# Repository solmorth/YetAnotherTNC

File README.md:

# YetAnotherTNC

Zephyr firmware (and, eventually, a companion PCB) for a nRF52840 Pro Micro
board that turns a phone's Bluetooth connection into a packet radio TNC.
Depending on how three GPIO pins are strapped at boot, the board acts as a
transparent UART↔BLE bridge, a real AX.25/KISS TNC driving 1200 baud Bell 202
AFSK audio (with optional FX.25 FEC), an AX.25 digipeater, or a standalone GPS
APRS tracker that beacons its position with no phone attached.

> **Early stage.** This has not been widely field-tested — one unit rides in
> the author's car and works there, but it hasn't been validated across
> different radios, conditions, or by other users. Treat it as a hobby
> project that works, not a hardened product.

No app or phone-side code lives in this repo — this is the board (and PCB)
side only. Anything that speaks BLE Nordic UART Service (NUS) and either raw
KISS or TNC2 monitor lines can talk to it; see [Phone app](#phone-app) below.

## Contents

- [Why](#why)
- [Hardware](#hardware)
  - [PCB](#pcb)
  - [Pinout](#pinout)
  - [Transceiver connector (JST 10-pin)](#transceiver-connector-jst-10-pin)
  - [Bill of Materials (BOM)](#bill-of-materials-bom)
- [Operating modes](#operating-modes)
- [Runtime configuration](#runtime-configuration)
- [Known limitations](#known-limitations)
- [Phone app](#phone-app)
- [Building](#building)
  - [Releases](#releases)
- [Testing](#testing)
- [Hardware-in-the-loop (HIL) test plan](#hardware-in-the-loop-hil-test-plan)
- [Repo layout](#repo-layout)
- [License](#license)

## Why

Cheap handheld radios generally don't have a KISS/TNC mode, and dedicated TNC
hardware is either bulky or costs more than the radio. This is a ~$10 nRF52840
board wired to a radio's mic/speaker/PTT lines, doing the AFSK modem and
AX.25 framing in software, with a phone or laptop over BLE instead of a serial
cable.

## Hardware

**Primary target: Yaesu FTM510.** The board's connector is designed to match
the FTM510's mic/data jack. The **FTM400 works out of the box** — same
connector, same signals. Any other radio that can be driven by its
mic/speaker/PTT lines can work too, via a custom audio interface cable
(not covered by this repo — just the pins on the nRF52840 side).

Board: Pro Micro nRF52840 (or any nice!nano-bootloader-compatible clone,
`promicro_nrf52840` in Zephyr).

### PCB

PCB design files and bill of materials live under [`pcb/`](pcb/) (`yatnc.kicad_sch`, `yatnc.kicad_pcb`, `yatnc.csv`).

| PCB 3D Render | PCB Editor |
|:---:|:---:|
|  |  |

### Pinout

| Pin | DT node | Function | Notes |
|---|---|---|---|
| 9, 10 (P0.09/P0.10) | `uart0` | Radio RS232 (APRS data) | Level-shifted through an onboard MAX3232 to true RS-232 (±12V). Primary use: the FTM510/FTM400's own built-in APRS packet decoder outputs RS232 here in BRIDGE mode. Also works with other serial-speaking radios/modems that expect a native protocol. Never touched by firmware for anything else. |
| 31 (P0.31) | `zephyr,user` io-channel | RX audio in | ADC (AIN7), sampled at 9600 Hz for the AFSK demodulator. |
| 20 (P0.20) | `&pwm0_default` | TX audio out | Hardware PWM carrier, low-pass filtered externally into an analog tone. |
| 22 (P0.22) | `ptt_pin` | PTT out | Active-high. |
| 2 (P0.02) | `mode_pin` | Mode select | Pull-up, active-low. Grounded → PACKET_TNC. |
| 29 (P0.29) | `digi_pin` | Digipeater select | Pull-up, active-low. Grounded → DIGIPEATER (overrides pin 2). |
| P1.15 | `standalone_pin` | Standalone GPS select | Pull-up, active-low. Grounded → STANDALONE (overrides pins 2 and 29). |
| P0.11 / P1.00 | `uart1` | GPS NMEA in | 9600 baud, TX / RX respectively (the GPS module's RX / TX). Only used in STANDALONE mode. |
| P1.04 | `gps_enable_pin` | GPS power enable | Active-high, pulled down. Driven high at boot in STANDALONE mode (unless a fixed position is configured). |

### Transceiver connector (JST 10-pin)

> [!IMPORTANT]
> - **RS-232 voltage levels (±12V)**: The serial lines on the 10-pin JST connector (`TO TRCV`) are true **RS-232 (±12V)** driven by the onboard MAX3232 transceiver, **not** 3.3V or 5V TTL. Do not connect them directly to logic-level UART pins!
> - **RX / TX crossover**: The RS-232 RX and TX lines **must be crossed** between the board's 10-pin JST connector and the radio (Board TX &rarr; Radio RX, Board RX &rarr; Radio TX).

| Pin | Net | Function / Description |
|:---:|---|---|
| 1 | `PKD` | TX Packet Audio (from PWM filter) |
| 2 | `GND` | Ground |
| 3 | `PTT` | PTT output |
| 4 | NC | Unconnected |
| 5 | `AUDIO TRCV` | RX Audio (to ADC demodulator) |
| 6 | NC | Unconnected |
| 7 | `RX` | RS-232 RX (±12V, connect to Radio TX — **crossed**) |
| 8 | `TX` | RS-232 TX (±12V, connect to Radio RX — **crossed**) |
| 9 | NC | Unconnected |
| 10 | NC | Unconnected |

### Bill of Materials (BOM)

Generated from KiCad BOM ([`pcb/yatnc.csv`](pcb/yatnc.csv)):

| Designator | Value / Part | Qty | Description |
|---|---|:---:|---|
| C1 | 270µF 35V | 1 | Polarized electrolytic capacitor |
| C2, C4, C7, C8, C9, C10, C11, C12 | 100nF | 8 | Ceramic disc capacitor |
| C3, C5 | 5.6nF | 2 | Ceramic disc capacitor |
| C6 | 470µF 10V | 1 | Polarized electrolytic capacitor |
| D1 | LPWR | 1 | Power indicator LED (5mm) |
| D2 | 1N5822 | 1 | Schottky diode (3A, 40V) |
| D3 | BZW04 18V | 1 | TVS transient voltage suppressor diode |
| D4 | LPTT | 1 | PTT indicator LED (5mm) |
| D5 | 1N4148 | 1 | High-speed switching diode |
| IC1 | MAX3232CDR | 1 | 3.3V/5V RS-232 transceiver (SOIC-16) |
| J1 | Conn_02x03_Top_Bottom | 1 | 2×3 pin header (2.54mm pitch) |
| J4 | DFR0570 | 1 | DFRobot DFR0570 DC-DC buck converter module |
| J5, J6 | Conn_01x13_Socket | 2 | 1×13 female socket headers (for Pro Micro nRF52840) |
| J7 | Conn_01x04_Pin | 1 | JST-EH 4-pin vertical header (2.50mm pitch) |
| PWR | Conn_01x02_Socket | 1 | JST-EH 2-pin vertical power connector (2.50mm pitch) |
| Q1, Q2 | BC547 | 2 | NPN bipolar junction transistor (TO-92) |
| R1, R3, R4, R5, R10 | 1k | 5 | Axial resistor 1kΩ (DIN0207) |
| R2 | 1ohm | 1 | Axial resistor 1Ω (DIN0207) |
| R6, R7, R8, R9 | 10k | 4 | Axial resistor 10kΩ (DIN0207) |
| SW1 | RST | 1 | Tactile push button switch (6mm) |
| TO TRCV | JST | 1 | JST-EH 10-pin vertical connector (to transceiver) |

### Transceiver connector (JST 10-pin)

> [!IMPORTANT]
> - **RS-232 voltage levels (±12V)**: The serial lines on the 10-pin JST connector (`TO TRCV`) are true **RS-232 (±12V)** driven by the onboard MAX3232 transceiver, **not** 3.3V or 5V TTL. Do not connect them directly to logic-level UART pins!
> - **RX / TX crossover**: The RS-232 RX and TX lines **must be crossed** between the board's 10-pin JST connector and the radio (Board TX &rarr; Radio RX, Board RX &rarr; Radio TX).

| Pin | Net | Function / Description |
|:---:|---|---|
| 1 | `PKD` | TX Packet Audio (from PWM filter) |
| 2 | `GND` | Ground |
| 3 | `PTT` | PTT output |
| 4 | NC | Unconnected |
| 5 | `AUDIO TRCV` | RX Audio (to ADC demodulator) |
| 6 | NC | Unconnected |
| 7 | `RX` | RS-232 RX (±12V, connect to Radio TX — **crossed**) |
| 8 | `TX` | RS-232 TX (±12V, connect to Radio RX — **crossed**) |
| 9 | NC | Unconnected |
| 10 | NC | Unconnected |

### Bill of Materials (BOM)

Generated from KiCad BOM ([`pcb/yatnc.csv`](pcb/yatnc.csv)):

| Designator | Value / Part | Qty | Description |
|---|---|:---:|---|
| C1 | 270µF 35V | 1 | Polarized electrolytic capacitor |
| C2, C4, C7, C8, C9, C10, C11, C12 | 100nF | 8 | Ceramic disc capacitor |
| C3, C5 | 5.6nF | 2 | Ceramic disc capacitor |
| C6 | 470µF 10V | 1 | Polarized electrolytic capacitor |
| D1 | LPWR | 1 | Power indicator LED (5mm) |
| D2 | 1N5822 | 1 | Schottky diode (3A, 40V) |
| D3 | BZW04 18V | 1 | TVS transient voltage suppressor diode |
| D4 | LPTT | 1 | PTT indicator LED (5mm) |
| D5 | 1N4148 | 1 | High-speed switching diode |
| IC1 | MAX3232CDR | 1 | 3.3V/5V RS-232 transceiver (SOIC-16) |
| J1 | Conn_02x03_Top_Bottom | 1 | 2×3 pin header (2.54mm pitch) |
| J4 | DFR0570 | 1 | DFRobot DFR0570 DC-DC buck converter module |
| J5, J6 | Conn_01x13_Socket | 2 | 1×13 female socket headers (for Pro Micro nRF52840) |
| J7 | Conn_01x04_Pin | 1 | JST-EH 4-pin vertical header (2.50mm pitch) |
| PWR | Conn_01x02_Socket | 1 | JST-EH 2-pin vertical power connector (2.50mm pitch) |
| Q1, Q2 | BC547 | 2 | NPN bipolar junction transistor (TO-92) |
| R1, R3, R4, R5, R10 | 1k | 5 | Axial resistor 1kΩ (DIN0207) |
| R2 | 1ohm | 1 | Axial resistor 1Ω (DIN0207) |
| R6, R7, R8, R9 | 10k | 4 | Axial resistor 10kΩ (DIN0207) |
| SW1 | RST | 1 | Tactile push button switch (6mm) |
| TO TRCV | JST | 1 | JST-EH 10-pin vertical connector (to transceiver) |

## Operating modes

The firmware selects one of four modes at boot (and re-checks live on every
packet) by reading the mode-select, digipeater-select and standalone-select pins above. There is
no software switch — the mode is purely hardware-strapped, and the pins are
read fresh on every packet, so mode can in principle change at runtime by
re-wiring the straps (no latching).

Resolution order (`mode_select_get_current()` in `src/mode_select.c`):

1. `standalone_pin` grounded → **STANDALONE**
2. else `digi_pin` grounded → **DIGIPEATER**
3. else `mode_pin` grounded → **PACKET_TNC**
4. else (all floating/high, the default) → **BRIDGE**

### 1. BRIDGE (default — all pins open)

A transparent, byte-for-byte serial bridge between the radio's RS232 (UART0)
and the phone app over BLE (NUS). No AX.25/KISS parsing, no AFSK, no PTT —
just raw bytes both directions.

This is primarily for **FTM510/FTM400 radios in their own native APRS
mode**: the radio decodes AFSK itself and emits packets over RS232, and this
mode just relays that (and any outgoing data) to/from the phone app. It also
works with any other radio/modem that expects to speak its own native serial
protocol (AT commands, firmware passthrough, etc.) rather than doing AX.25
packet radio in this firmware.

- **Radio → App**: `uart_isr` (main.c) collects UART0 RX bytes into a ring
  buffer; 50ms after the line goes idle, `process_uart_to_ble()` sends
  whatever accumulated straight out over BLE notify.
- **App → Radio**: `nus_received()` queues whatever the app wrote straight to
  the TX queue; the TX thread writes it byte-by-byte to UART0 via
  `uart_poll_out()`.

### 2. PACKET_TNC (`mode_pin` grounded)

A real AX.25 KISS TNC. The app talks AX.25/KISS over BLE; the radio side is
driven as 1200 baud Bell 202 AFSK audio (with optional FX.25 forward error
correction), not raw serial.

**App → Radio (TX)**, in `tnc_process_ble_bytes()`:

1. Bytes from BLE are fed into a persistent KISS decoder. A full KISS frame
   (`FEND ... FEND`) is only acted on once its closing `FEND` has actually
   arrived — a frame split across several BLE writes (common: phones write
   in ~20-byte ATT chunks before MTU negotiation) is reassembled correctly
   before anything is sent.
2. Most phone APRS apps don't actually KISS-frame anything — they write a
   human-readable **TNC2 monitor line** instead, e.g.
   `SP3LSN-9>APVEC0,WIDE1-1,WIDE2-1:!5227.76N/01654.03E>comment`. If nothing
   KISS-decodes within 250ms of the app going idle, `tnc_send_raw_frame()`
   tries `ax25_parse_monitor()` on the accumulated bytes; on success it
   builds a real binary AX.25 UI frame (proper shifted-ASCII addresses,
   control/PID, FCS) instead of transmitting the raw text. If it doesn't
   parse either way, the bytes are assumed to already be a raw AX.25 frame
   and sent as-is.
3. If a stray `FEND` byte appears in non-KISS app data (e.g. a Latin-1
   accented character in an APRS comment happens to be `0xC0`) and never
   gets a matching closing `FEND`, the KISS decoder used to wedge itself
   in-frame forever, silently swallowing everything after it. It now
   self-resets after the same 250ms idle window instead.
4. Every queued frame is picked up by the TX thread: PTT keys (pin 22,
   active-high), the frame is modulated to AFSK PCM (`AFSKModulator`, with
   FX.25 RS(255,239) wrapping if enabled via `audio_tx_set_fx25(true)` —
   off by default, no live control path wired to it yet), the waveform is
   played out on pin 20 via the nRF52840's hardware PWM, then PTT unkeys.

**Radio → App (RX)**, two independent sources feed the same BLE output:

- **Audio demodulation**: a dedicated thread samples pin 31 (ADC, AIN7) at
  9600Hz through `AFSKDemodulator` (bandpass filter → frequency discriminator
  → DPLL bit recovery → HDLC flag/destuff, with an FX.25 correlation-tag
  correlator running in parallel that transparently Reed-Solomon-corrects a
  frame if the sender wrapped it in FX.25). A decoded frame is KISS-wrapped
  and sent over BLE.
- **UART0**: if the radio/modem itself emits KISS bytes over serial rather
  than raw audio, `tnc_process_radio_bytes()` decodes and forwards those the
  same way.

### 3. DIGIPEATER (`digi_pin` grounded, overrides `mode_pin`)

Everything PACKET_TNC does, plus: every frame heard on the radio is checked
for an un-repeated `WIDEn-N`/`DIGI` hop in its path
(`digipeat_process_frame()`). If found, the hop's SSID is decremented (H-bit
set once it reaches 0, marking it used) and the frame is re-encoded and
re-transmitted back out over radio — a standard WIDEn-N digipeater. The frame
is forwarded to the BLE app either way, repeated or not, so the app sees
everything heard on the channel.

### 4. STANDALONE (`standalone_pin` grounded, overrides the other two)

A GPS APRS tracker. The board beacons its position over the radio on a timer,
with no phone needed. Otherwise it behaves like PACKET_TNC (the BLE app can
still connect, send frames, and change [settings](#runtime-configuration)).

- **Live GPS** (default): at boot the firmware powers the GPS module
  (`gps_enable_pin`) and reads NMEA from `uart1`. `$GPGGA`/`$GNGGA` sentences
  are parsed for fix state and position. The first fix starts the beacon; it
  then repeats every `BEACON` seconds while the fix is held, using the most
  recent position. No fix (or fix lost) → nothing is transmitted.
- **Fixed position**: with `SET FIXEDPOS=ON` (and both `LAT`/`LON` set) the
  GPS module is never powered or touched. The stored coordinates are beaconed
  on the same interval, starting once the TX pipeline is up. Handy indoors or
  with no GPS fitted. Until both coordinates are set, nothing is sent.
- **Beacon format**: an uncompressed APRS position report (`!DDMM.hhN/DDDMM.hhE>` + comment)
  from your callsign to `APRS`, primary-table car symbol (`/>`), sent through the
  normal TX path (PTT → AFSK → PWM).

## Runtime configuration

Callsign, beacon interval, comment and fixed position are set at runtime with
single-line ASCII commands sent as KISS command `0x06` (`KISS_CMD_SETHARDWARE`)
over BLE. Each command is applied immediately, saved to flash, and answered
with a KISS `0x06` frame carrying the reply text. Errors are reported in the
reply (`ERR ...`), never as a dropped connection. Settings survive reboots.

| Command | Effect | Default |
|---|---|---|
| `SET CALL=N0CALL-9` | Source callsign for beacons | `N0CALL` |
| `SET BEACON=120` | Beacon interval in seconds (clamped to 10–3600) | `60` |
| `SET COMMENT=text` | Beacon comment (truncated to 32 chars) | empty |
| `SET FIXEDPOS=ON\|OFF` | Beacon a stored position instead of using GPS | `OFF` |
| `SET LAT=52.4627` / `SET LON=16.9005` | Fixed position, decimal degrees | unset |
| `GET` | Reply with all current values | |

The settings live in a 32 KiB NVS partition at `0x90000` (see `app.overlay`),
deliberately clear of the UF2 bootloader. The BLE device name is `YATNC`.

## Known limitations

- **AFSK decode is functional but not polished.** It works, but weak-signal
  / low-level decode robustness needs more work — expect some missed frames
  on marginal audio until the demodulator gets more tuning.
- **Not widely field-tested.** Verified on the bench and in one car; not yet
  validated across multiple radios, RF conditions, or users.
- FX.25 TX wrapping has no live control path yet (`audio_tx_set_fx25`, code
  only).
- STANDALONE mode parses GGA sentences only, with no altitude, speed/course or
  compressed positions in the beacon. The symbol is fixed to the car icon.
- The `SET`/`GET` config commands are not yet exposed in any phone app; send
  them yourself as KISS `0x06` frames.

## Phone app

Developed and tested against **[aprsvector](https://aprsvector.ores.one)**
(also by the author) — that's the reference app for this firmware and the
one to reach for first.

More generally, anything that speaks BLE Nordic UART Service (NUS) and
either raw KISS or TNC2 monitor lines *should* work (most Android APRS apps
fit this description), but only aprsvector has actually been tested against
this firmware.

## Building

```sh
./build.sh
```

First run creates a `.venv`, pulls a Zephyr workspace into `zephyrproject/`
(via `west`), and builds for `promicro_nrf52840`. Later runs reuse both, so
they're much faster. Pass anything after the script name straight through to
`west build` if you need non-default args:

```sh
./build.sh -b promicro_nrf52840 --pristine
```

If no usable Zephyr SDK is found (it looks in `.zephyr-sdk/`,
`~/zephyr-sdk-*`, `/opt/zephyr-sdk-*`, etc, and checks that CMake and the ARM
compiler are actually present), the script downloads a minimal one into
`.zephyr-sdk/` and sets up the `arm-zephyr-eabi` toolchain. Set
`ZEPHYR_SDK_INSTALL_DIR` to use your own instead.

Output is `build/zephyr/zephyr.uf2`. To flash: double-tap the board's reset
button to drop into the UF2 bootloader (it'll show up as a USB drive), then
copy the file over. Boards need the nice!nano / Adafruit UF2 bootloader
already installed.

### Releases

Pushing a version tag (`1.2.3` or `v1.2.3`) triggers
`.github/workflows/release.yml`, which runs the host tests, builds the
firmware, and publishes a GitHub release with `yatnc-<tag>.uf2` attached, so
you can flash without building.

```sh
git tag 1.2.3 && git push origin 1.2.3
```

## Testing

```sh
./run_tests.sh
```

Builds and runs the host-side unit tests for everything that doesn't touch
Zephyr or real hardware — AX.25, KISS, FX.25, GPS/NMEA formatting, and the AFSK modem DSP — and
fails if line coverage on any of those drops below 80%. `tnc.c`, `main.c`,
`ptt.c`, `mode_select.c`, `gps.c`, `tnc_config.c`, and the audio drivers aren't covered here; they need
a board, see [HIL test plan](#hardware-in-the-loop-hil-test-plan).

There's also a Python reference model of the AFSK modem
(`tools/afsk_dsp.py`, tested by `tools/test_afsk.py`/`pytest`) used to
sanity-check the C++ implementation and to generate/analyze WAV captures
independent of the firmware.

## Hardware-in-the-loop (HIL) test plan

`run_tests.sh` covers the Zephyr-free pure-logic modules (AX.25, KISS, FX.25,
GPS formatting, AFSK modem DSP) at ≥80% line coverage on host. It cannot touch anything that
only exists on real silicon: GPIO strapping, hardware PWM audio out, ADC
audio in, UART timing, or BLE NUS. Those need the actual `promicro_nrf52840`
board. This is a plan, not a runnable suite yet — no board rig is set up for
automated HIL runs.

What each untestable-on-host module needs:

1. **`mode_select.c`** — ground/float P0.02, P0.29 and P1.15 in each
   combination, reboot, confirm `mode_select_get_current()`/boot log report
   BRIDGE / PACKET_TNC / DIGIPEATER / STANDALONE correctly, and that re-strapping is
   picked up live (no latching).
2. **`ptt.c`** — scope P0.22 across a TX; confirm it goes active-high only
   for the duration `audio_tx_pwm` is actually playing samples, and idles
   low the rest of the time (a PTT stuck high keys the radio permanently).
3. **`audio_tx_pwm.cpp`** — scope P0.20; confirm the PWM carrier frequency
   and the external low-pass filter actually pass 1200/2200 Hz clean and
   knock the PWM carrier down enough that an external TNC (or this board's
   own RX path, looped back) decodes it.
4. **`audio_rx_adc.cpp`** — feed a known AFSK signal into P0.31 (from a
   signal generator, or TX pin of a second unit looped back through the
   filter) and confirm frames make it out over BLE.
5. **RS232 bridge (BRIDGE mode, `main.c`)** — with a real FTM510/FTM400 (or
   other serial device) on P0.09/P0.10 through the onboard MAX3232, confirm
   byte-for-byte passthrough both directions and the 50ms idle-flush timing.
6. **BLE NUS end-to-end** — a phone/PC BLE client sends a KISS frame or
   TNC2 monitor line; confirm it comes out the radio side per the routing
   already unit-tested at the `ax25.c`/`kiss.c` level, and vice versa.
7. **`gps.c`** — in STANDALONE mode with a GPS module on P0.11/P1.00, confirm
   P1.04 goes high at boot, NMEA shows in the log, and a beacon goes out
   after the first fix and again every `BEACON` seconds. With
   `FIXEDPOS=ON`, confirm P1.04 stays low and the stored position beacons.
8. **`tnc_config.c`** — send each `SET`/`GET` command over BLE, confirm the
   reply, power-cycle, and confirm values persist. Confirm the UF2 bootloader
   still works afterwards (NVS must not touch it).
9. **Full loop**: two boards, one PACKET_TNC and one DIGIPEATER, over actual
   RF or a dummy-load/attenuator link — confirms the whole AFSK+FX.25+KISS
   stack end to end, not just each half in isolation on host.

Implementing an automated HIL rig (e.g. Zephyr `twister --hardware-map`) is a
follow-up once there's dedicated bench hardware for it; for now these are run
by hand.

## Repo layout

```
src/            firmware source (Zephyr app)
tools/          host-side Python tooling (AFSK reference model, WAV decoder, log capture)
app.overlay     devicetree overlay: GPIO straps, GPS UART/enable, ADC channel, PWM pin, NVS partition
prj.conf        Zephyr/Kconfig options
CMakeLists.txt  build target sources
build.sh        one-shot Zephyr workspace + SDK + build
run_tests.sh    host-side unit tests + coverage
.github/        CI: tag-triggered release workflow
gerber/         PCB fabrication files
pcb/            KiCad board design files and BOM (yatnc.kicad_sch, yatnc.kicad_pcb, yatnc.csv)
images/         PCB 3D render and layout editor screenshots
```

Other tools in `tools/`:

- `decode_aprs.py` — decodes AX.25/APRS frames out of a captured WAV file, for checking a TX recording without a second TNC.
- `capture_log.ps1` — tails the board's USB serial console to a timestamped log file, reconnecting automatically across board resets (handy for catching a crash dump).

## License

`src/main.c` carries an `SPDX-License-Identifier: Apache-2.0` header; treat
the rest of the firmware the same way unless noted otherwise.

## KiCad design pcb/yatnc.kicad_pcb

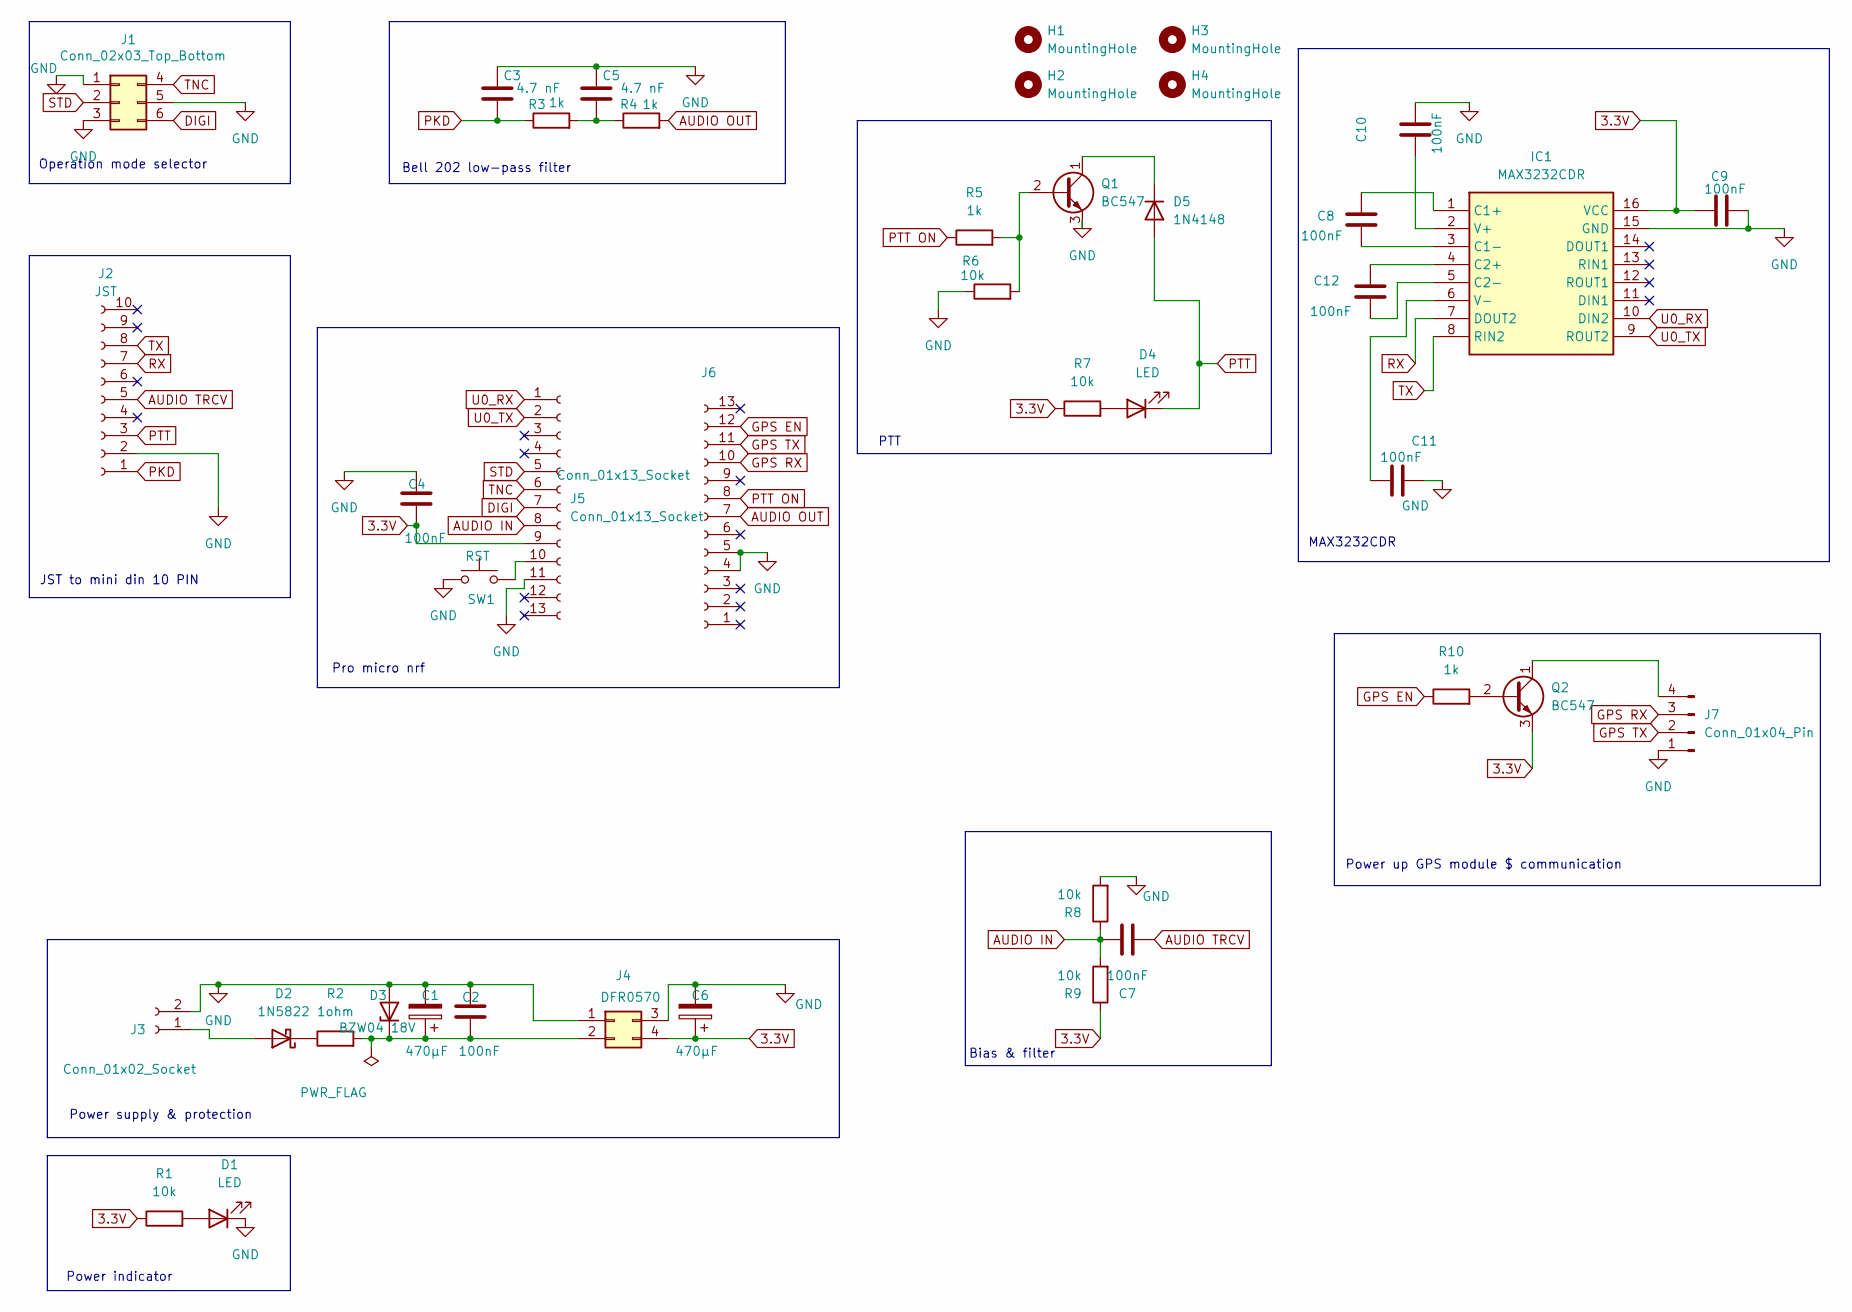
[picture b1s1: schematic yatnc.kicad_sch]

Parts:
C1, C6: 470µF; CP_Radial_D8.0mm_P5.00mm
C2, C4, C7, C8, C9, C10, C11, C12: 100nF; C_Disc_D5.0mm_W2.5mm_P5.00mm
C3, C5: 4.7 nF; C_Disc_D5.0mm_W2.5mm_P5.00mm
D1, D4: LED; LED_D5.0mm
D2: 1N5822; D_DO-201AD_P15.24mm_Horizontal
D3: BZW04 18V; D_DO-15_P10.16mm_Horizontal
D5: 1N4148; D_DO-35_SOD27_P7.62mm_Horizontal
H1, H2, H3, H4: MountingHole; MountingHole_3.2mm_M3
IC1: MAX3232CDR; SOIC127P600X175-16N; Mouser Part Number 595-MAX3232CDR
J1: Conn_02x03_Top_Bottom; PinHeader_2x03_P2.54mm_Vertical
J2: JST; JST_EH_B10B-EH-A_1x10_P2.50mm_Vertical
J3: Conn_01x02_Socket; JST_EH_B2B-EH-A_1x02_P2.50mm_Vertical
J4: DFR0570; dfr0570
J5, J6: Conn_01x13_Socket; PinSocket_1x13_P2.54mm_Vertical
J7: Conn_01x04_Pin; JST_EH_B4B-EH-A_1x04_P2.50mm_Vertical
Q1, Q2: BC547; TO-92_Inline_Wide
R1, R6, R7, R8, R9: 10k; R_Axial_DIN0207_L6.3mm_D2.5mm_P10.16mm_Horizontal
R2: 1ohm; R_Axial_DIN0207_L6.3mm_D2.5mm_P10.16mm_Horizontal
R3, R4, R5, R10: 1k; R_Axial_DIN0207_L6.3mm_D2.5mm_P10.16mm_Horizontal
SW1: RST; SW_PUSH_6mm

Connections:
3.3V: C4.2, C6.1, C9.1, IC1.16 (VCC), J4.4, J5.9, Q2.3 (E), R1.1, R7.1, R9.1
AUDIO IN: C7.2, J5.8, R8.1, R9.2
AUDIO OUT: J6.7, R4.2
AUDIO TRCV: C7.1, J2.5; also elsewhere on the board
DIGI: J1.6, J5.7
GND: C1.2, C2.1, C3.1, C4.1, C5.1, C6.2, C9.2, C10.2, C11.1, D1.1 (K), D3.2 (A), IC1.15 (GND), J1.1, J1.3, J1.5, J2.2, J3.2, J4.1, J4.3, J5.11, J6.4, J6.5, J7.1, Q1.3 (E), R6.1, R8.2, SW1.1; also elsewhere on the board
GPS EN: J6.12, R10.1
GPS RX: J6.10, J7.3
GPS TX: J6.11, J7.2
unnamed: C5.2, R3.2, R4.1
unnamed: D1.2 (A), R1.2
unnamed 11: D2.2 (A), J3.1; also elsewhere on the board
unnamed: D2.1 (K), R2.1
unnamed: C1.1, C2.2, D3.1 (K), J4.2, R2.2
unnamed: D4.2 (A), R7.2
unnamed: D5.1 (K), Q1.1 (C)
unnamed: C8.1, IC1.1 (C1+)
unnamed: C8.2, IC1.3 (C1-)
unnamed: C12.1, IC1.4 (C2+)
unnamed: C12.2, IC1.5 (C2-)
unnamed: C10.1, IC1.2 (V+)
unnamed: C11.2, IC1.6 (V-)
unnamed: J5.10, SW1.2
unnamed: J7.4, Q2.1 (C)
unnamed: Q1.2 (B), R5.2, R6.2
unnamed: Q2.2 (B), R10.2
PKD: C3.2, J2.1, R3.1; also elsewhere on the board
PTT: D4.1 (K), D5.2 (A), J2.3; also elsewhere on the board
PTT ON: J6.8, R5.1
RX: IC1.7 (DOUT2), J2.7; also elsewhere on the board
STD: J1.2, J5.5
TNC: J1.4, J5.6
TX: IC1.8 (RIN2), J2.8; also elsewhere on the board
U0_RX: IC1.10 (DIN2), J5.1
U0_TX: IC1.9 (ROUT2), J5.2

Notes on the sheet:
MAX3232CDR
Operation mode selector
Power up GPS module $ communication
Power supply & protection
Bias & filter
Power indicator
JST to mini din 10 PIN
PTT
Bell 202 low-pass filter
Pro micro nrf

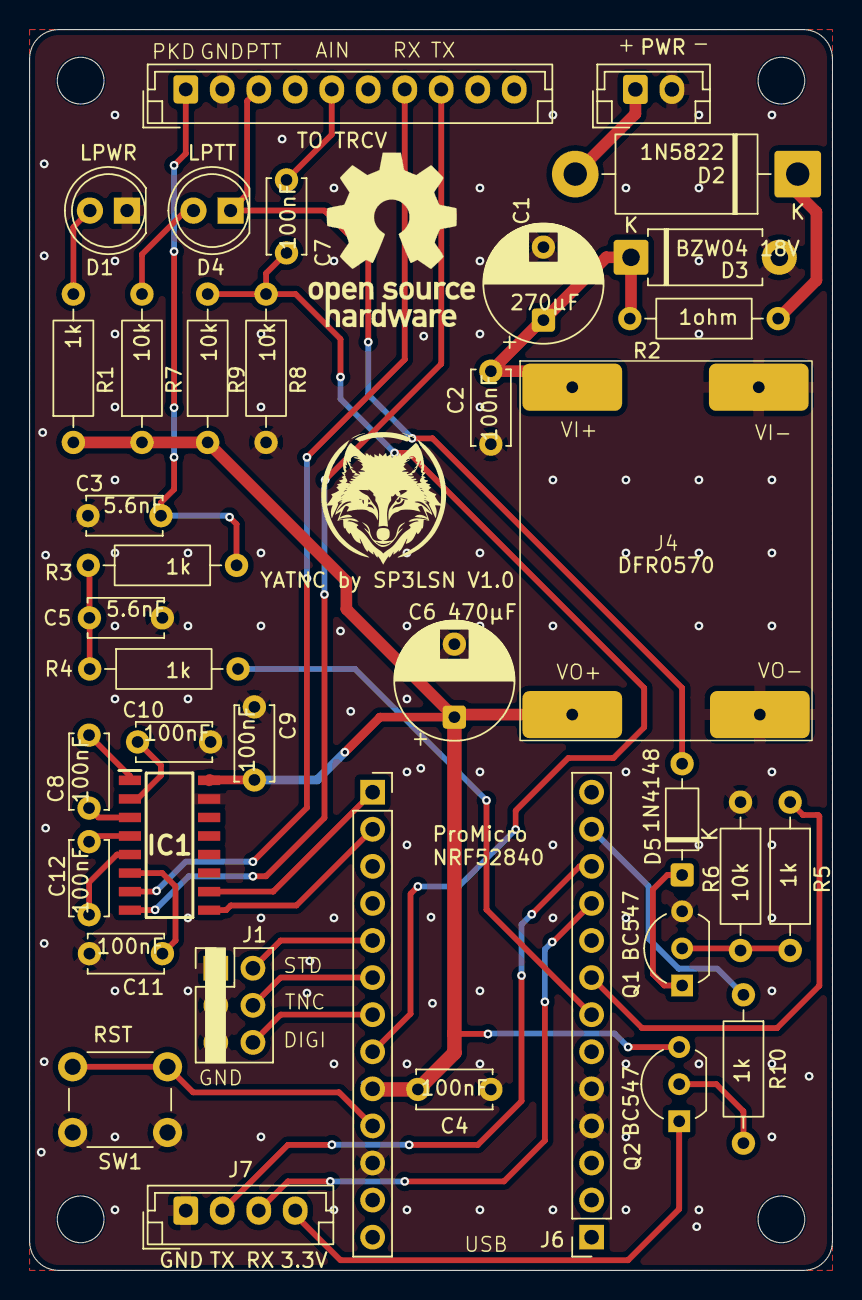
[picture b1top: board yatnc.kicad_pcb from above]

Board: 2 copper layers, 55.0 x 85.0 mm, 42 parts (0 on the bottom side), 35 nets.

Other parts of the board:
PWR: Conn_01x02_Socket; JST_EH_B2B-EH-A_1x02_P2.50mm_Vertical
TO TRCV: JST; JST_EH_B10B-EH-A_1x10_P2.50mm_Vertical

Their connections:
AUDIO TRCV: TO TRCV.5; also elsewhere on the board
GND: PWR.2, TO TRCV.2; also elsewhere on the board
unnamed 11: PWR.1; also elsewhere on the board
PKD: TO TRCV.1; also elsewhere on the board
PTT: TO TRCV.3; also elsewhere on the board
RX: TO TRCV.7; also elsewhere on the board
TX: TO TRCV.8; also elsewhere on the board
